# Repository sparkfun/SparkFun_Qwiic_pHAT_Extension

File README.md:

SparkFun Raspberry Pi 400 Qwiic pHAT Extension
========================================

[*SparkFun Raspberry Pi 400 Qwiic pHAT Extension (DEV-17512)*](https://www.sparkfun.com/products/17512)

<Basic description of the part.>

Repository Contents
-------------------

* **/Hardware** - Eagle design files (.brd, .sch)
* **/Production** - Production panel files (.brd)

Documentation
--------------
* **[Qwiic Py](https://github.com/sparkfun/Qwiic_Py)** - Python packages for Qwiic-enabled devices
* **[Hookup Guide](https://learn.sparkfun.com/tutorials/raspberry-pi-400-qwiic-phat-extension-hookup-guide)** - Basic hookup guide for the <PRODUCT NAME>.

Product Versions
----------------
* [DEV-17512](https://www.sparkfun.com/products/17512)

Version History
---------------
* [v1.0](URL for tag specific to this version) - Initial Release

License Information
-------------------

This product is _**open source**_! 

Please review the LICENSE.md file for license information. 

If you have any questions or concerns on licensing, please contact technical support on our [SparkFun forums](https://forum.sparkfun.com/viewforum.php?f=152).

Distributed as-is; no warranty is given.

- Your friends at SparkFun.

_<COLLABORATION CREDIT>_

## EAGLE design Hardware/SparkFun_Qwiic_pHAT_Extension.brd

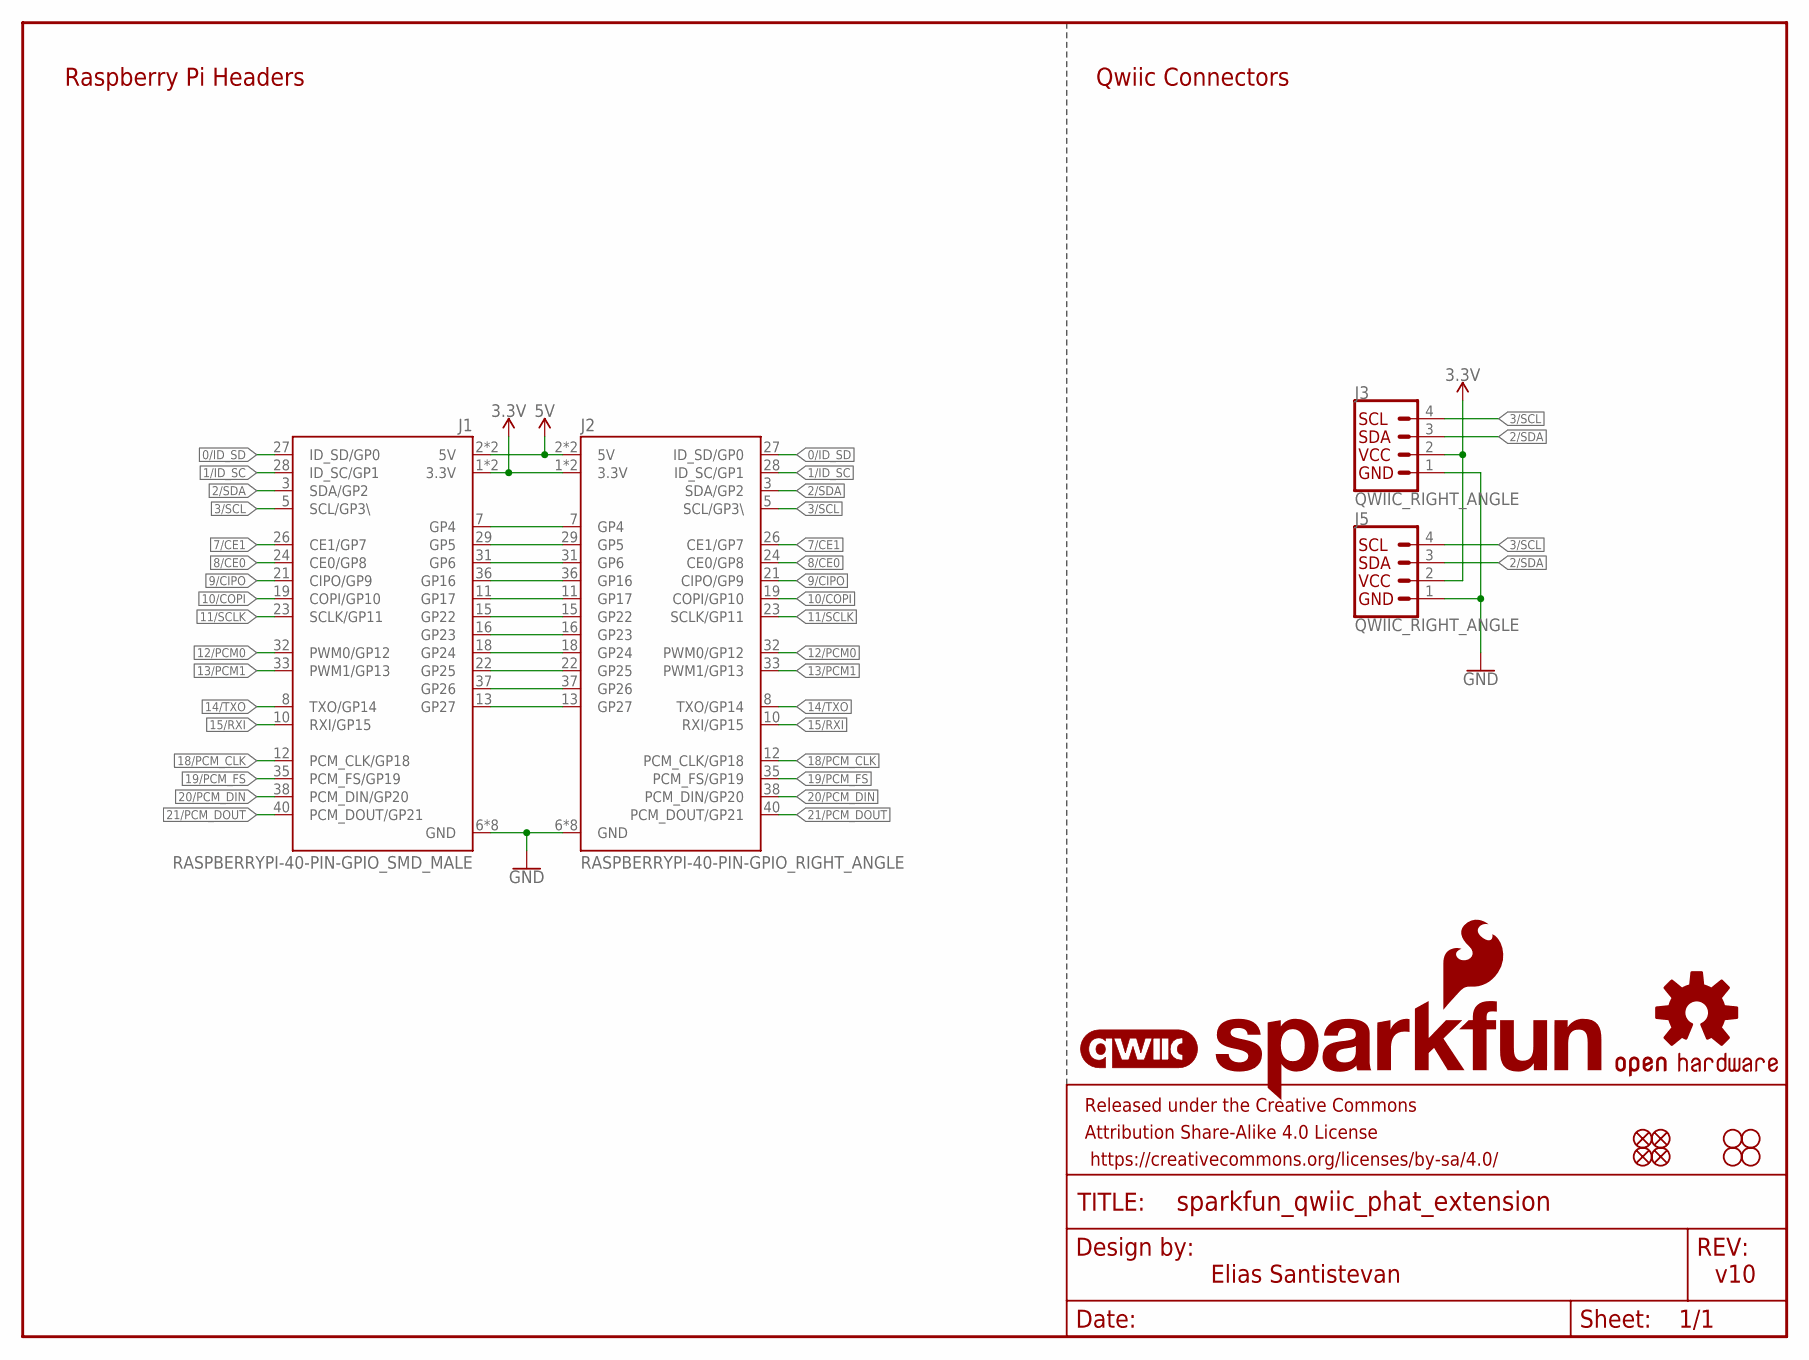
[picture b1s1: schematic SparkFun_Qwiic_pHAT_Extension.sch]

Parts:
FD1, FD2, FD3, FD4: FIDUCIALUFIDUCIAL; FIDUCIAL-MICRO
FRAME1: FRAME-LETTER; CREATIVE_COMMONS
H1, H2, H3, H4: STAND-OFFTIGHT; STAND-OFF-TIGHT
J1: RASPBERRYPI-40-PIN-GPIO_SMD_MALE; RASPBERRY_PI_HAT_40_PIN_SMD_MALE
J2: RASPBERRYPI-40-PIN-GPIO_RIGHT_ANGLE; 2X20_RIGHT_ANGLE
J3, J5: QWIIC_RIGHT_ANGLE; JST04_1MM_RA
LOGO1: QWIIC_LOGO_5MM; QWIIC_5MM
LOGO2: SFE_LOGO_NAME_FLAME.2_INCH; SFE_LOGO_NAME_FLAME_.2
LOGO3: OSHW-LOGOM; OSHW-LOGO-M

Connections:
0/ID_SD: J1.27 (ID_SD/GP0), J2.27 (ID_SD/GP0)
1/ID_SC: J1.28 (ID_SC/GP1), J2.28 (ID_SC/GP1)
2/SDA: J1.3 (SDA/GP2), J2.3 (SDA/GP2), J3.3, J5.3
3.3V: J1.1 (3.3V), J1.17 (3.3V), J2.1 (3.3V), J2.17 (3.3V), J3.2, J5.2
3/SCL: J1.5 (SCL/GP3\), J2.5 (SCL/GP3\), J3.4, J5.4
5V: J1.2 (5V), J1.4 (5V), J2.2 (5V), J2.4 (5V)
7/CE1: J1.26 (CE1/GP7), J2.26 (CE1/GP7)
8/CE0: J1.24 (CE0/GP8), J2.24 (CE0/GP8)
9/CIPO: J1.21 (CIPO/GP9), J2.21 (CIPO/GP9)
10/COPI: J1.19 (COPI/GP10), J2.19 (COPI/GP10)
11/SCLK: J1.23 (SCLK/GP11), J2.23 (SCLK/GP11)
12/PWM0: J1.32 (PWM0/GP12), J2.32 (PWM0/GP12)
13/PWM1: J1.33 (PWM1/GP13), J2.33 (PWM1/GP13)
14/TXO: J1.8 (TXO/GP14), J2.8 (TXO/GP14)
15/RXI: J1.10 (RXI/GP15), J2.10 (RXI/GP15)
18/PCM_CLK: J1.12 (PCM_CLK/GP18), J2.12 (PCM_CLK/GP18)
19/PCM_FS: J1.35 (PCM_FS/GP19), J2.35 (PCM_FS/GP19)
20/PCM_DIN: J1.38 (PCM_DIN/GP20), J2.38 (PCM_DIN/GP20)
21/PCM_DOUT: J1.40 (PCM_DOUT/GP21), J2.40 (PCM_DOUT/GP21)
GND: J1.6 (GND), J1.9 (GND), J1.14 (GND), J1.20 (GND), J1.25 (GND), J1.30 (GND), J1.34 (GND), J1.39 (GND), J2.6 (GND), J2.9 (GND), J2.14 (GND), J2.20 (GND), J2.25 (GND), J2.30 (GND), J2.34 (GND), J2.39 (GND), J3.1, J5.1
GP4: J1.7 (GP4), J2.7 (GP4)
GP5: J1.29 (GP5), J2.29 (GP5)
GP6: J1.31 (GP6), J2.31 (GP6)
GP16: J1.36 (GP16), J2.36 (GP16)
GP17: J1.11 (GP17), J2.11 (GP17)
GP22: J1.15 (GP22), J2.15 (GP22)
GP23: J1.16 (GP23), J2.16 (GP23)
GP24: J1.18 (GP24), J2.18 (GP24)
GP25: J1.22 (GP25), J2.22 (GP25)
GP26: J1.37 (GP26), J2.37 (GP26)
GP27: J1.13 (GP27), J2.13 (GP27)

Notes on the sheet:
Elias Santistevan
v10
Qwiic Connectors
Raspberry Pi Headers

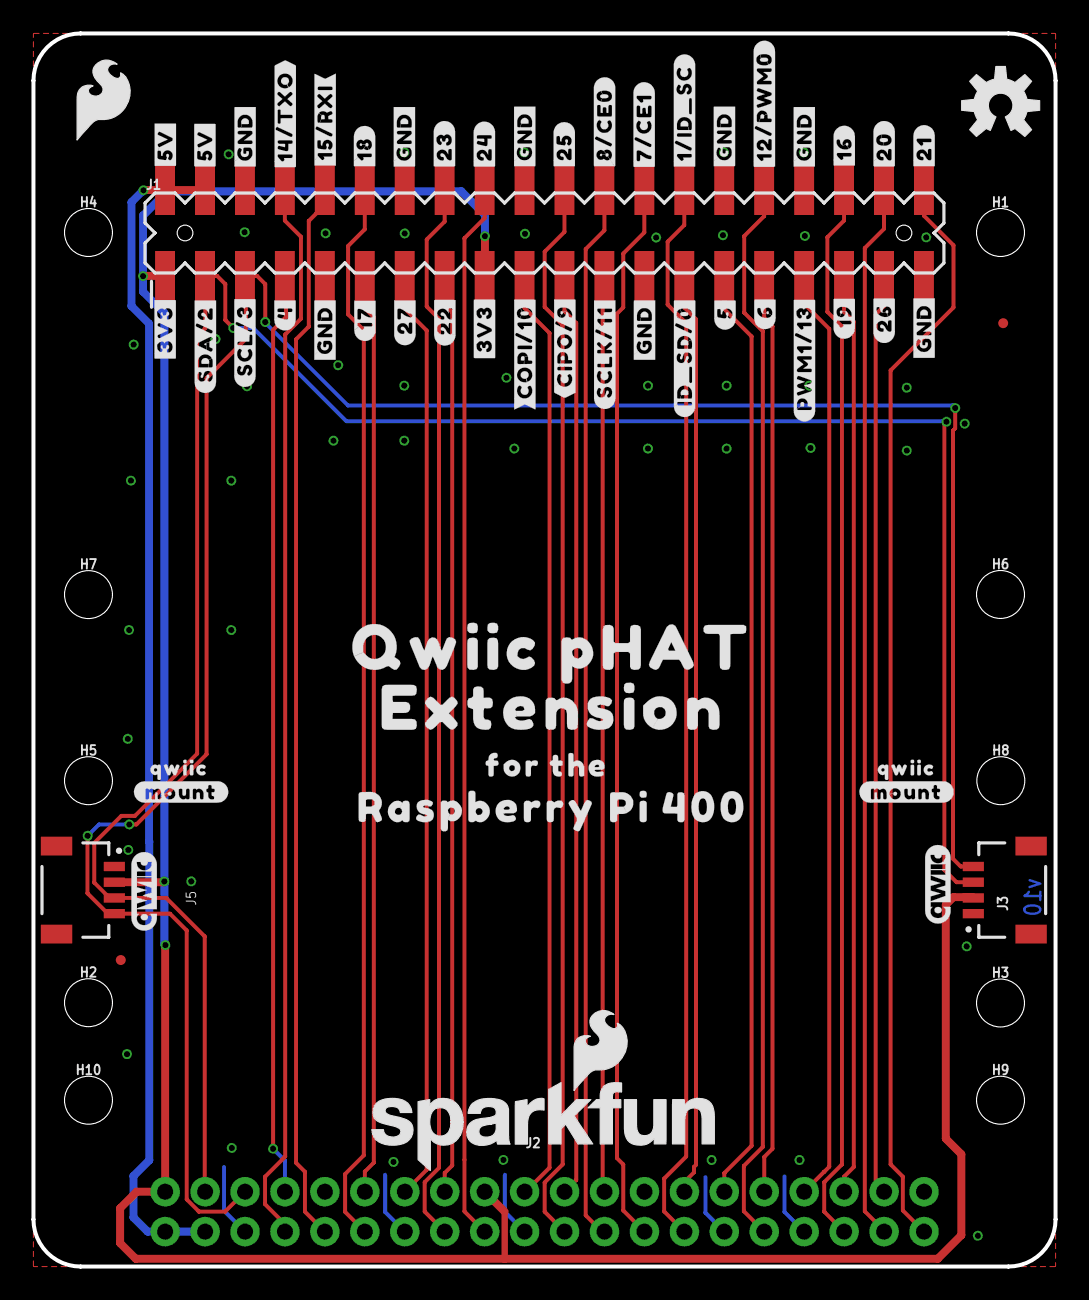
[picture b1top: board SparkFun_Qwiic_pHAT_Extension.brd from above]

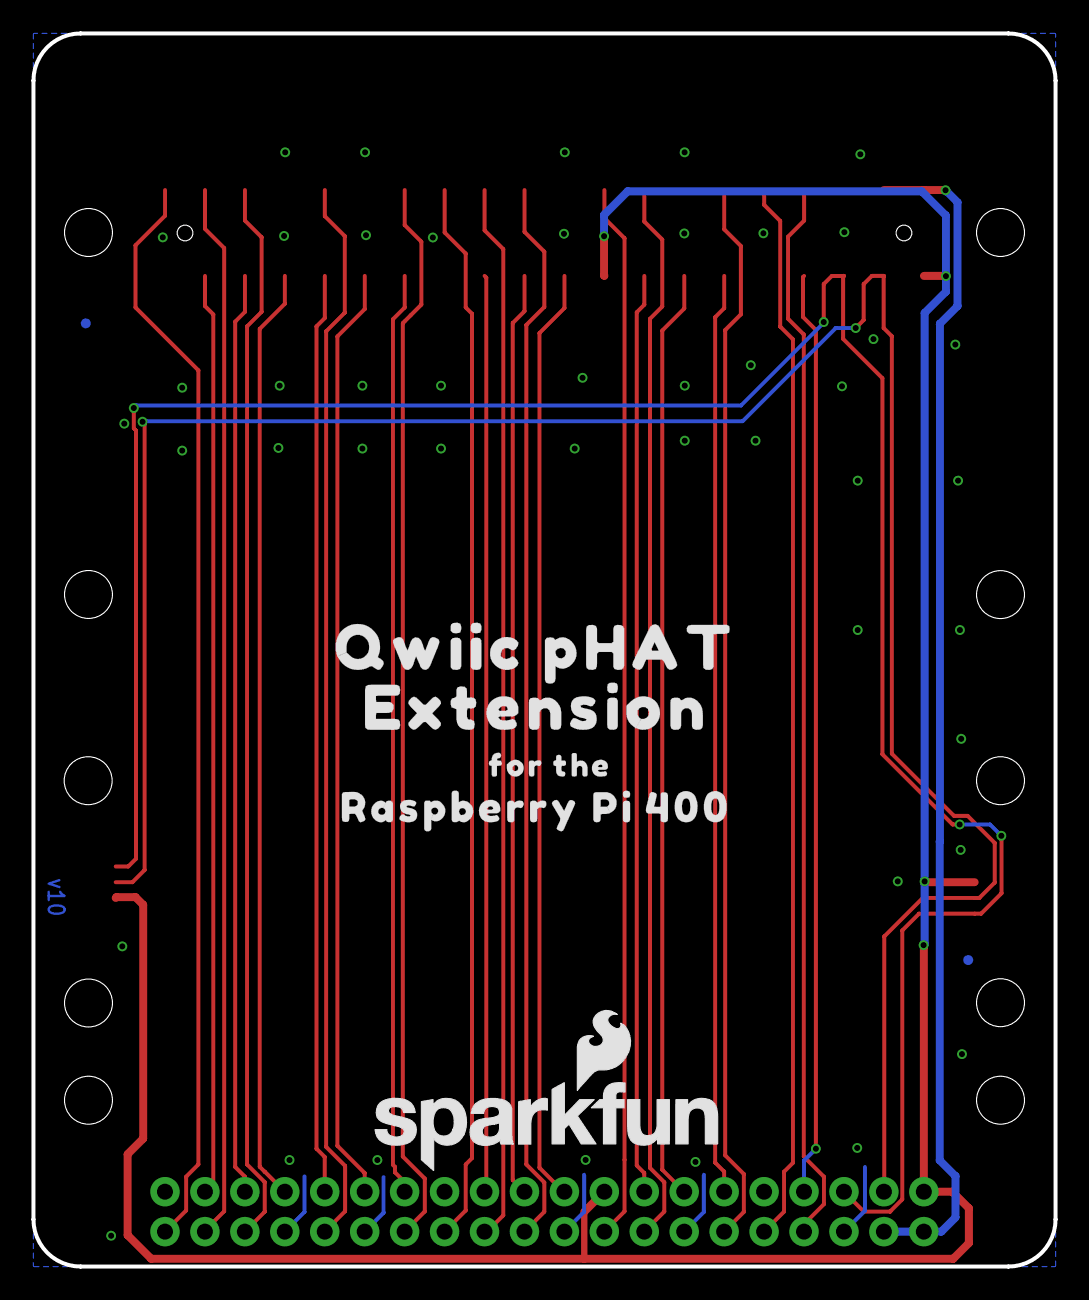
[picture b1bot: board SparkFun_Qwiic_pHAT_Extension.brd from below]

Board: 2 copper layers, 65.0 x 78.4 mm, 77 parts (7 on the bottom side), 31 nets.

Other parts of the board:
H5, H6, H7, H8, H9, H10: STAND-OFFTIGHT; STAND-OFF-TIGHT
LOGO4: QWIIC_LOGO_5MM; QWIIC_5MM
LOGO5: SFE_LOGO_NAME_FLAME.2_INCH; SFE_LOGO_NAME_FLAME_.2
U$1: #SDA#2#4
U$2: #SCL#3#4
U$3, U$13: FOR_THE40034
U$4, U$5: #3V3#0
U$6: #4#4
U$7: #5#28
U$8, U$9: #5V#28
U$10: #6#28
U$11: #7#CE1#29
U$12: #8#CE0#29
U$14: #SCLK#11#28
U$15: #ID_SD#0#28
U$16: #12#PWM0#29
U$17: #PWM1#13#28
U$18: #14#TXO#29
U$19: #15#RXI#29
U$20: #16#29
U$21: #17#5
U$22: #18#29
U$23: #19#28
U$24: #20#29
U$25: #21#29
U$26: #22#28
U$27: #23#29
U$28: #24#29
U$29: #25#29
U$30: #26#28
U$31: #27#18
U$32, U$33, U$34, U$35, U$36, U$37, U$38, U$39: #GND#28
U$40: #1#ID_SC#29
U$51: #CIPO#9#28
U$52: #COPI#10#28
U$75, U$89: QWIIC_PHAT31
U$76, U$90: EXTENSION32
U$81: SFE_LOGO_FLAME_.2
U$82, U$83: #MOUNT#29
U$84, U$85: QWIIC30
U$86, U$91: RASPBERRY_PI_40033

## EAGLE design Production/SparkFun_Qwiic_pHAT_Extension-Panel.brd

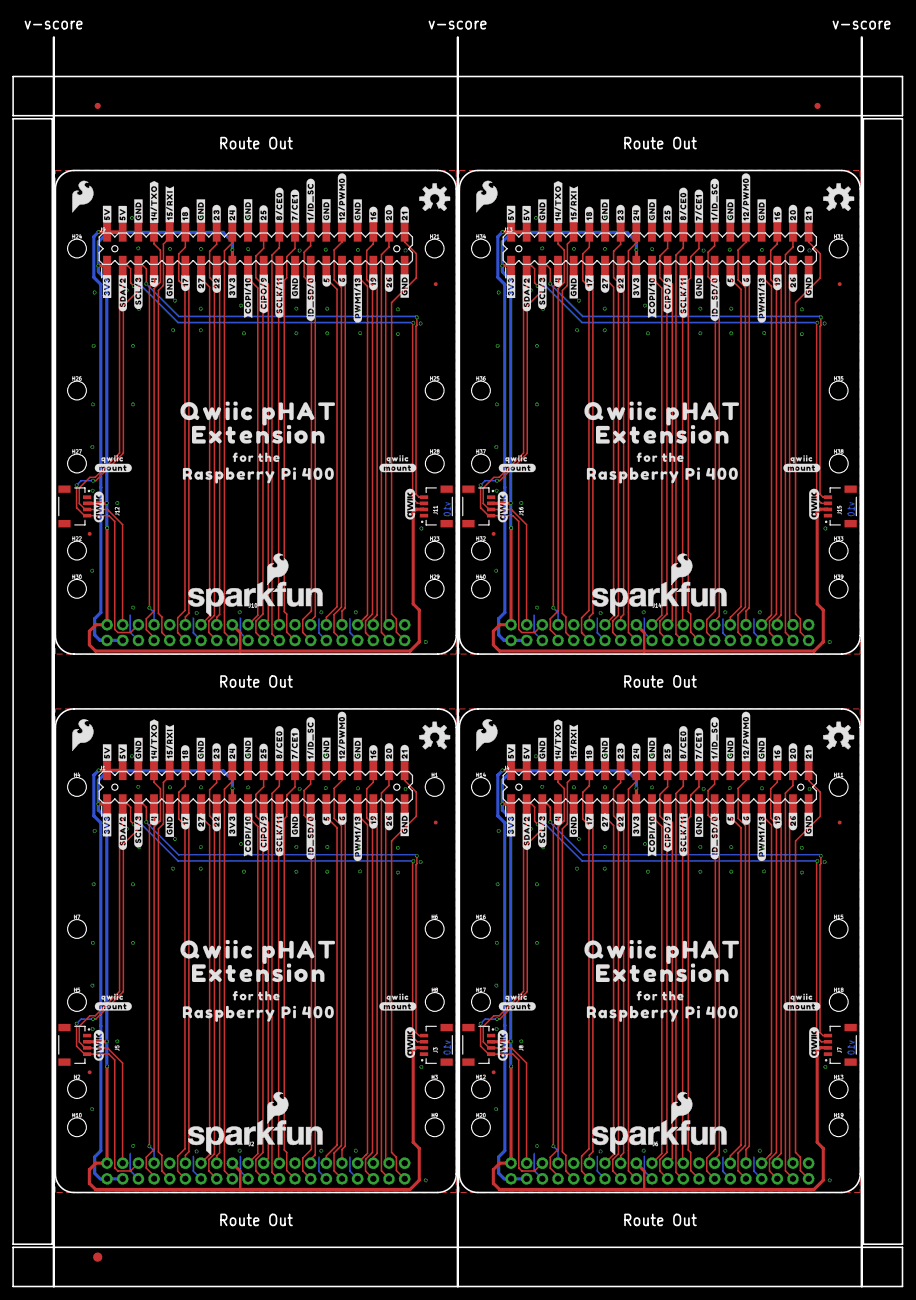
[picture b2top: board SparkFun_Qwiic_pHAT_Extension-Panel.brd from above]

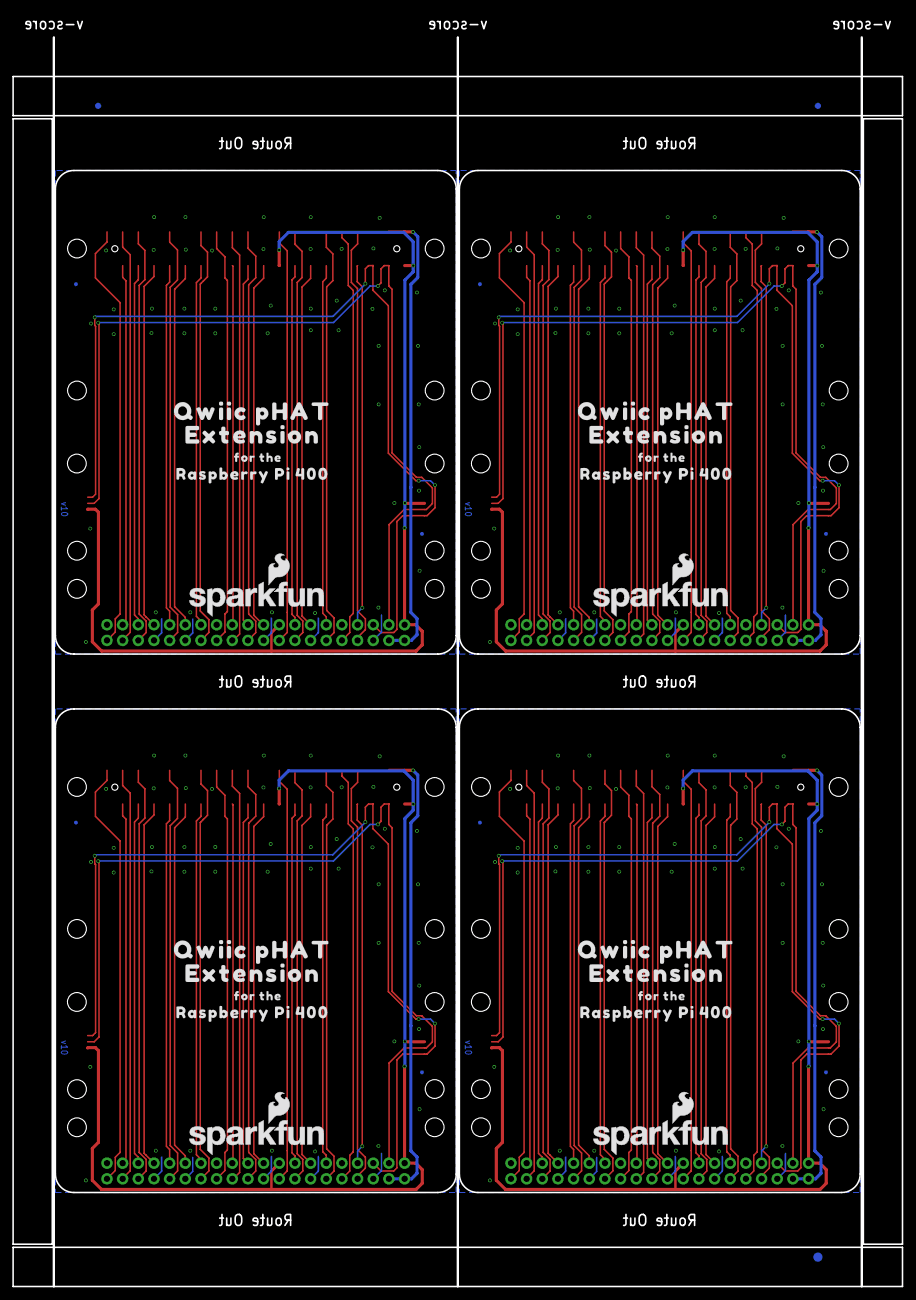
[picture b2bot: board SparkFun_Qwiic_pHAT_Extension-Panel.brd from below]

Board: 2 copper layers, 144.1 x 206.4 mm, 310 parts (31 on the bottom side), 124 nets.

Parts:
E$1, E$2, E$3, E$4: FIDUCIAL-1X2
E$5, E$6: FIDUCIAL-1.5X3
FD1, FD2, FD3, FD4, FD5, FD6, FD7, FD8, FD9, FD10, FD11, FD12, FD13, FD14, FD15, FD16: FIDUCIALUFIDUCIAL; FIDUCIAL-MICRO
H1, H2, H3, H4, H5, H6, H7, H8, H9, H10, H11, H12, H13, H14, H15, H16, H17, H18, H19, H20, H21, H22, H23, H24, H25, H26, H27, H28, H29, H30, H31, H32, H33, H34, H35, H36, H37, H38, H39, H40: STAND-OFFTIGHT; STAND-OFF-TIGHT
J1, J4, J9, J13: RASPBERRYPI-40-PIN-GPIO_SMD_MALE; RASPBERRY_PI_HAT_40_PIN_SMD_MALE
J2, J6, J10, J14: RASPBERRYPI-40-PIN-GPIO_RIGHT_ANGLE; 2X20_RIGHT_ANGLE
J3, J5, J7, J8, J11, J12, J15, J16: QWIIC_RIGHT_ANGLE; JST04_1MM_RA
LOGO1, LOGO4, LOGO6, LOGO9, LOGO11, LOGO14, LOGO16, LOGO19: QWIIC_LOGO_5MM; QWIIC_5MM
LOGO2, LOGO5, LOGO7, LOGO10, LOGO12, LOGO15, LOGO17, LOGO20: SFE_LOGO_NAME_FLAME.2_INCH; SFE_LOGO_NAME_FLAME_.2
LOGO3, LOGO8, LOGO13, LOGO18: OSHW-LOGOM; OSHW-LOGO-M
U$1, U$74, U$138, U$191: #SDA#2#4
U$2, U$77, U$139, U$192: #SCL#3#4
U$3, U$13, U$105, U$106, U$158, U$159, U$211, U$212: FOR_THE40034
U$4, U$5, U$41, U$42, U$107, U$108, U$160, U$161: #3V3#0
U$6, U$43, U$109, U$162: #4#4
U$7, U$44, U$110, U$163: #5#28
U$8, U$9, U$45, U$46, U$111, U$112, U$164, U$165: #5V#28
U$10, U$47, U$113, U$166: #6#28
U$11, U$48, U$114, U$167: #7#CE1#29
U$12, U$49, U$115, U$168: #8#CE0#29
U$14, U$78, U$140, U$193: #SCLK#11#28
U$15, U$79, U$141, U$194: #ID_SD#0#28
U$16, U$50, U$116, U$169: #12#PWM0#29
U$17, U$80, U$142, U$195: #PWM1#13#28
U$18, U$97, U$150, U$203: #14#TXO#29
U$19, U$98, U$151, U$204: #15#RXI#29
U$20, U$53, U$117, U$170: #16#29
U$21, U$54, U$118, U$171: #17#5
U$22, U$55, U$119, U$172: #18#29
U$23, U$56, U$120, U$173: #19#28
U$24, U$57, U$121, U$174: #20#29
U$25, U$58, U$122, U$175: #21#29
U$26, U$59, U$123, U$176: #22#28
U$27, U$60, U$124, U$177: #23#29
U$28, U$61, U$125, U$178: #24#29
U$29, U$62, U$126, U$179: #25#29
U$30, U$63, U$127, U$180: #26#28
U$31, U$64, U$128, U$181: #27#18
U$32, U$33, U$34, U$35, U$36, U$37, U$38, U$39, U$65, U$66, U$67, U$68, U$69, U$70, U$71, U$72, U$129, U$130, U$131, U$132, U$133, U$134, U$135, U$136, U$182, U$183, U$184, U$185, U$186, U$187, U$188, U$189: #GND#28
U$40, U$73, U$137, U$190: #1#ID_SC#29
U$51, U$88, U$144, U$197: #CIPO#9#28
U$52, U$92, U$145, U$198: #COPI#10#28
U$75, U$89, U$99, U$102, U$152, U$155, U$205, U$208: QWIIC_PHAT31
U$76, U$90, U$100, U$103, U$153, U$156, U$206, U$209: EXTENSION32
U$81, U$87, U$143, U$196: SFE_LOGO_FLAME_.2
U$82, U$83, U$93, U$94, U$146, U$147, U$199, U$200: #MOUNT#29
U$84, U$85, U$95, U$96, U$148, U$149, U$201, U$202: QWIIC30
U$86, U$91, U$101, U$104, U$154, U$157, U$207, U$210: RASPBERRY_PI_40033

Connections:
0/ID_SD: J1.27, J2.27
0/ID_SD1: J4.27, J6.27
0/ID_SD2: J9.27, J10.27
0/ID_SD3: J13.27, J14.27
1/ID_SC: J1.28, J2.28
1/ID_SC1: J4.28, J6.28
1/ID_SC2: J9.28, J10.28
1/ID_SC3: J13.28, J14.28
2/SDA: J1.3, J2.3, J3.3, J5.3
2/SDA1: J4.3, J6.3, J7.3, J8.3
2/SDA2: J9.3, J10.3, J11.3, J12.3
2/SDA3: J13.3, J14.3, J15.3, J16.3
3.3V: J1.1, J1.17, J2.1, J2.17, J3.2, J5.2
3.3V1: J4.1, J4.17, J6.1, J6.17, J7.2, J8.2
3.3V2: J9.1, J9.17, J10.1, J10.17, J11.2, J12.2
3.3V3: J13.1, J13.17, J14.1, J14.17, J15.2, J16.2
3/SCL: J1.5, J2.5, J3.4, J5.4
3/SCL1: J4.5, J6.5, J7.4, J8.4
3/SCL2: J9.5, J10.5, J11.4, J12.4
3/SCL3: J13.5, J14.5, J15.4, J16.4
5V: J1.2, J1.4, J2.2, J2.4
5V1: J4.2, J4.4, J6.2, J6.4
5V2: J9.2, J9.4, J10.2, J10.4
5V3: J13.2, J13.4, J14.2, J14.4
7/CE1: J1.26, J2.26
7/CE2: J4.26, J6.26
7/CE3: J9.26, J10.26
7/CE4: J13.26, J14.26
8/CE0: J1.24, J2.24
8/CE1: J4.24, J6.24
8/CE2: J9.24, J10.24
8/CE3: J13.24, J14.24
9/CIPO: J1.21, J2.21
9/CIPO1: J4.21, J6.21
9/CIPO2: J9.21, J10.21
9/CIPO3: J13.21, J14.21
10/COPI: J1.19, J2.19
10/COPI1: J4.19, J6.19
10/COPI2: J9.19, J10.19
10/COPI3: J13.19, J14.19
11/SCLK: J1.23, J2.23
11/SCLK1: J4.23, J6.23
11/SCLK2: J9.23, J10.23
11/SCLK3: J13.23, J14.23
12/PWM0: J1.32, J2.32
12/PWM1: J4.32, J6.32
12/PWM2: J9.32, J10.32
12/PWM3: J13.32, J14.32
13/PWM1: J1.33, J2.33
13/PWM2: J4.33, J6.33
13/PWM3: J9.33, J10.33
13/PWM4: J13.33, J14.33
14/TXO: J1.8, J2.8
14/TXO1: J4.8, J6.8
14/TXO2: J9.8, J10.8
14/TXO3: J13.8, J14.8
15/RXI: J1.10, J2.10
15/RXI1: J4.10, J6.10
15/RXI2: J9.10, J10.10
15/RXI3: J13.10, J14.10
18/PCM_CLK: J1.12, J2.12
18/PCM_CLK1: J4.12, J6.12
18/PCM_CLK2: J9.12, J10.12
18/PCM_CLK3: J13.12, J14.12
19/PCM_FS: J1.35, J2.35
19/PCM_FS1: J4.35, J6.35
19/PCM_FS2: J9.35, J10.35
19/PCM_FS3: J13.35, J14.35
20/PCM_DIN: J1.38, J2.38
20/PCM_DIN1: J4.38, J6.38
20/PCM_DIN2: J9.38, J10.38
20/PCM_DIN3: J13.38, J14.38
21/PCM_DOUT: J1.40, J2.40
21/PCM_DOUT1: J4.40, J6.40
21/PCM_DOUT2: J9.40, J10.40
21/PCM_DOUT3: J13.40, J14.40
GND: J1.6, J1.9, J1.14, J1.20, J1.25, J1.30, J1.34, J1.39, J2.6, J2.9, J2.14, J2.20, J2.25, J2.30, J2.34, J2.39, J3.1, J5.1
GND1: J4.6, J4.9, J4.14, J4.20, J4.25, J4.30, J4.34, J4.39, J6.6, J6.9, J6.14, J6.20, J6.25, J6.30, J6.34, J6.39, J7.1, J8.1
GND2: J9.6, J9.9, J9.14, J9.20, J9.25, J9.30, J9.34, J9.39, J10.6, J10.9, J10.14, J10.20, J10.25, J10.30, J10.34, J10.39, J11.1, J12.1
GND3: J13.6, J13.9, J13.14, J13.20, J13.25, J13.30, J13.34, J13.39, J14.6, J14.9, J14.14, J14.20, J14.25, J14.30, J14.34, J14.39, J15.1, J16.1
GP1: J4.7, J6.7
GP2: J4.29, J6.29
GP3: J4.31, J6.31
GP4: J1.7, J2.7
GP5: J1.29, J2.29
GP6: J1.31, J2.31
GP7: J4.36, J6.36
GP8: J4.11, J6.11
GP9: J4.15, J6.15
GP10: J4.16, J6.16
GP11: J4.18, J6.18
GP12: J4.22, J6.22
GP13: J4.37, J6.37
GP14: J4.13, J6.13
GP15: J9.7, J10.7
GP16: J1.36, J2.36
GP17: J1.11, J2.11
GP18: J9.29, J10.29
GP19: J9.31, J10.31
GP20: J9.36, J10.36
GP21: J9.11, J10.11
GP22: J1.15, J2.15
GP23: J1.16, J2.16
GP24: J1.18, J2.18
GP25: J1.22, J2.22
GP26: J1.37, J2.37
GP27: J1.13, J2.13
GP28: J9.15, J10.15
GP29: J9.16, J10.16
GP30: J9.18, J10.18
GP31: J9.22, J10.22
GP32: J9.37, J10.37
GP33: J9.13, J10.13
GP34: J13.7, J14.7
GP35: J13.29, J14.29
GP36: J13.31, J14.31
GP37: J13.36, J14.36
GP38: J13.11, J14.11
GP39: J13.15, J14.15
GP40: J13.16, J14.16
GP41: J13.18, J14.18
GP42: J13.22, J14.22
GP43: J13.37, J14.37
GP44: J13.13, J14.13

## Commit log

2020-10-23 Updates symbol which required an entire reroute of the board
    * Adds "qwiic mount" silk
    * moves Qwiic connector "lower" on the board to align with standoffs
    * Adds standoffs for micro-hats
2020-10-23 Swaps the rows of PTH holes on the right angle connector
2020-10-26 Adds name to board
2020-10-26 Removes labels from underneath the board
2020-10-26 Adds "for the" silk, shrinks SparkFun logo
2020-10-26 Adds better measures
2020-10-26 Removes extra Tdocu lines
2020-10-26 Adds a single GND via
2020-10-27 Moves standoffs for Qwiic mount because it would have interfered with micro Raspberry hats
2020-10-27 Updates the names of the eagle files to correct name, adds license, readme, etc
2020-10-27 Fixes PWM net names, fixes measures to account for moved stand offs
2020-10-27 Adds 2x2 production panel
2020-10-27 Moves fiducials on the panel to the attached portions of the panel frame

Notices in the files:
parts and their libraries:
SparkFun-Aesthetics: Licensing: Creative Commons ShareAlike 4.0 International - https://creativecommons.org/licenses/by-sa/4.0
SparkFun-Aesthetics: Released under the Creative Commons Attribution Share-Alike 4.0 License
SparkFun-Aesthetics: https://creativecommons.org/licenses/by-sa/4.0
